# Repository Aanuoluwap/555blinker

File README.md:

# 555 Blinker & ESP32 Projects

This repository contains electronics design projects created using KiCad.

## Projects

### 1. 555 Blinker (Root)

A classic Astable Multivibrator circuit using the NE555 timer IC.

**Components:**
- **U1**: NE555D (SOIC-8)
- **R1**: 1kΩ Resistor (1206)
- **R2**: 68kΩ Resistor (1206)
- **R3**: 8.2kΩ Resistor (1206)
- **C2**: 10µF Tantalum Capacitor (EIA-3216-18)
- **D1**: LED (1206)
- **J1**: 1x02 Pin Header (2.54mm)

**Function:**
The circuit is configured as an astable multivibrator, flashing the LED (D1). The frequency is determined by R2, R3, and C2.

### 2. Project 2: ESP32 Build

Located in `Priject_2__ESP32_build/`.

This project involves an ESP32 microcontroller.
*(Further details to be added)*

## Directory Structure

```
.
├── 555 blinker.kicad_pro    # 555 Blinker Project File
├── 555 blinker.kicad_sch    # Schematic
├── 555 blinker.kicad_pcb    # PCB Layout
└── Priject_2__ESP32_build/  # ESP32 Project Folder
```

## Tools Used

- **KiCad EDA**: [https://www.kicad.org/](https://www.kicad.org/) (Version 8.0 or later recommended)

## License

This project is licensed under the MIT License - see the [LICENSE](LICENSE) file for details.

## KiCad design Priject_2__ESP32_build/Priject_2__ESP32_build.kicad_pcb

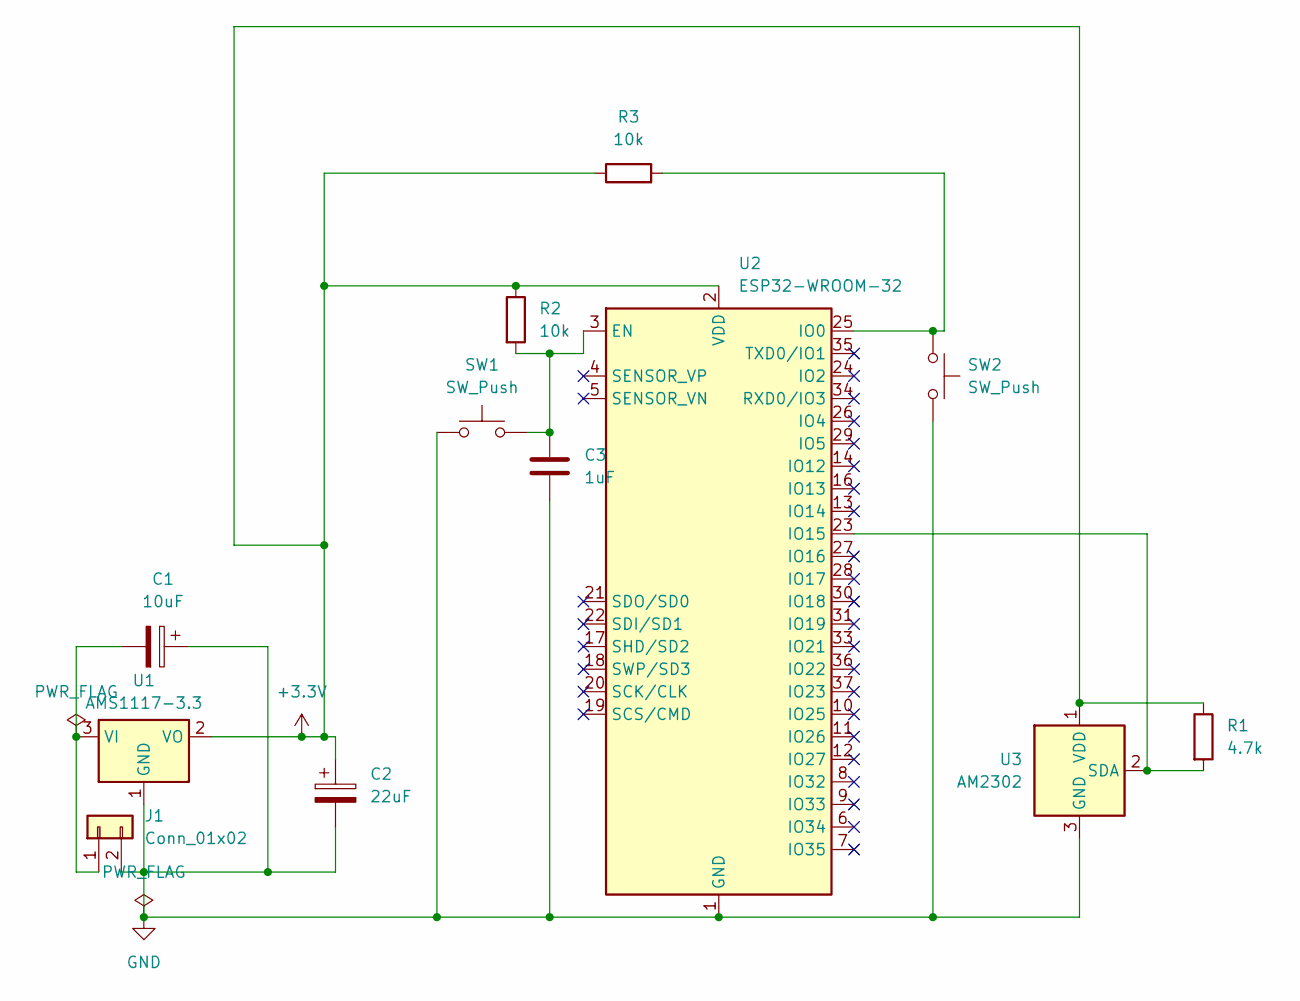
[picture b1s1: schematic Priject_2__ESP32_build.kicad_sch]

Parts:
C1: 10uF; CP_EIA-3216-18_Kemet-A
C2: 22uF; CP_EIA-3216-18_Kemet-A
C3: 1uF; CP_EIA-3216-18_Kemet-A
J1: Conn_01x02; PinHeader_1x02_P2.54mm_Vertical_SMD_Pin1Right
R1: 4.7k; R_1206_3216Metric
R2, R3: 10k; R_1206_3216Metric
SW1, SW2: SW_Push; SW_DIP_SPSTx02_Slide_9.78x7.26mm_W8.61mm_P2.54mm
U1: AMS1117-3.3; SOT-223-3_TabPin2
U2: ESP32-WROOM-32
U3: AM2302; ASAIR_AM2302_P2.54mm_Vertical

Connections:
+3.3V: C2.1, R1.1, R2.1, R3.1, U1.2 (VO), U2.2 (VDD), U3.1 (VDD)
GND: C1.1, C2.2, C3.2, J1.2, SW1.1, SW2.2, U1.1 (GND), U2.1 (GND), U2.15 (GND), U2.38 (GND), U2.39 (GND), U3.3 (GND), U3.4 (GND)
unnamed: C1.2, J1.1, U1.3 (VI)
unnamed: C3.1, R2.2, SW1.2, U2.3 (EN)
unnamed: R3.2, SW2.1, U2.25 (IO0)
unnamed: R1.2, U2.23 (IO15), U3.2 (SDA)

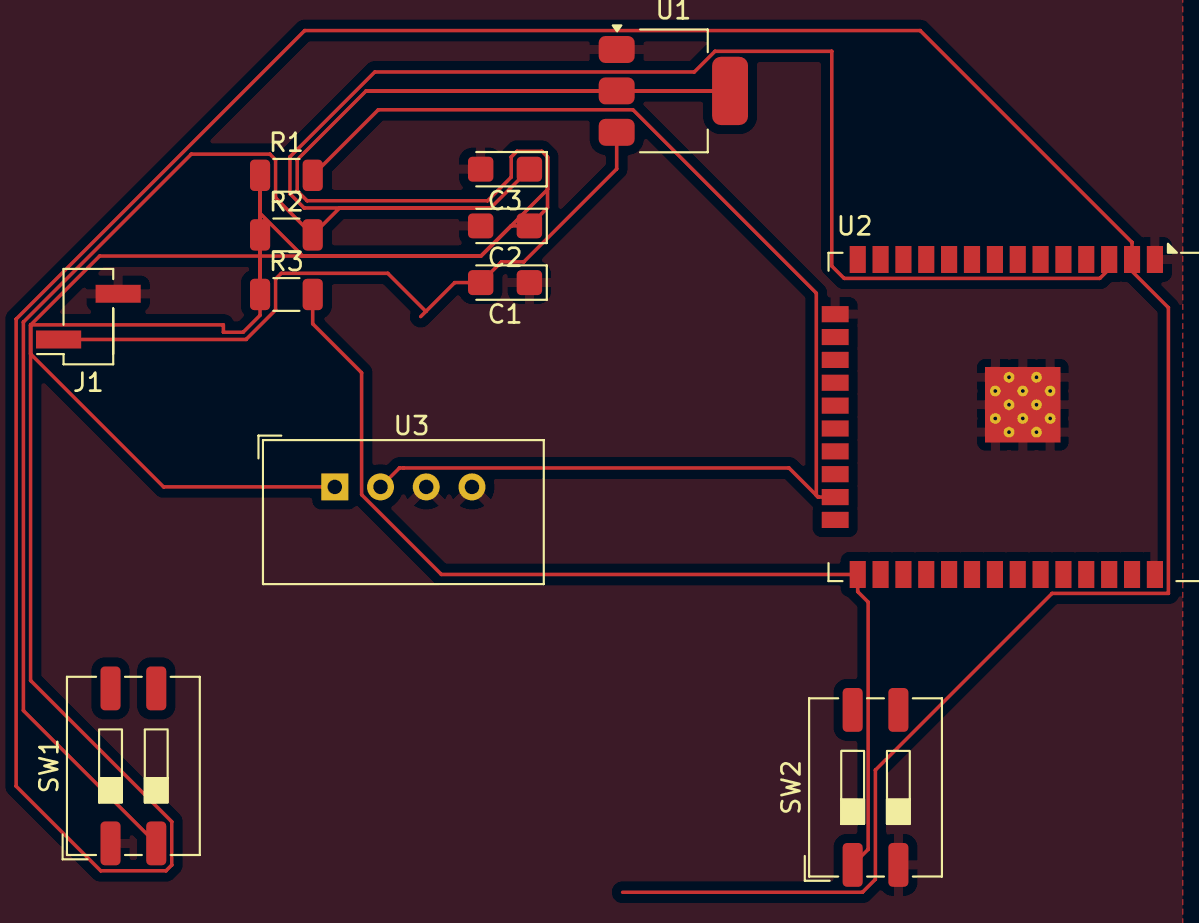
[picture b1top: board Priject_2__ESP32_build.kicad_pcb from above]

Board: 2 copper layers, 12 parts (0 on the bottom side), 6 nets.

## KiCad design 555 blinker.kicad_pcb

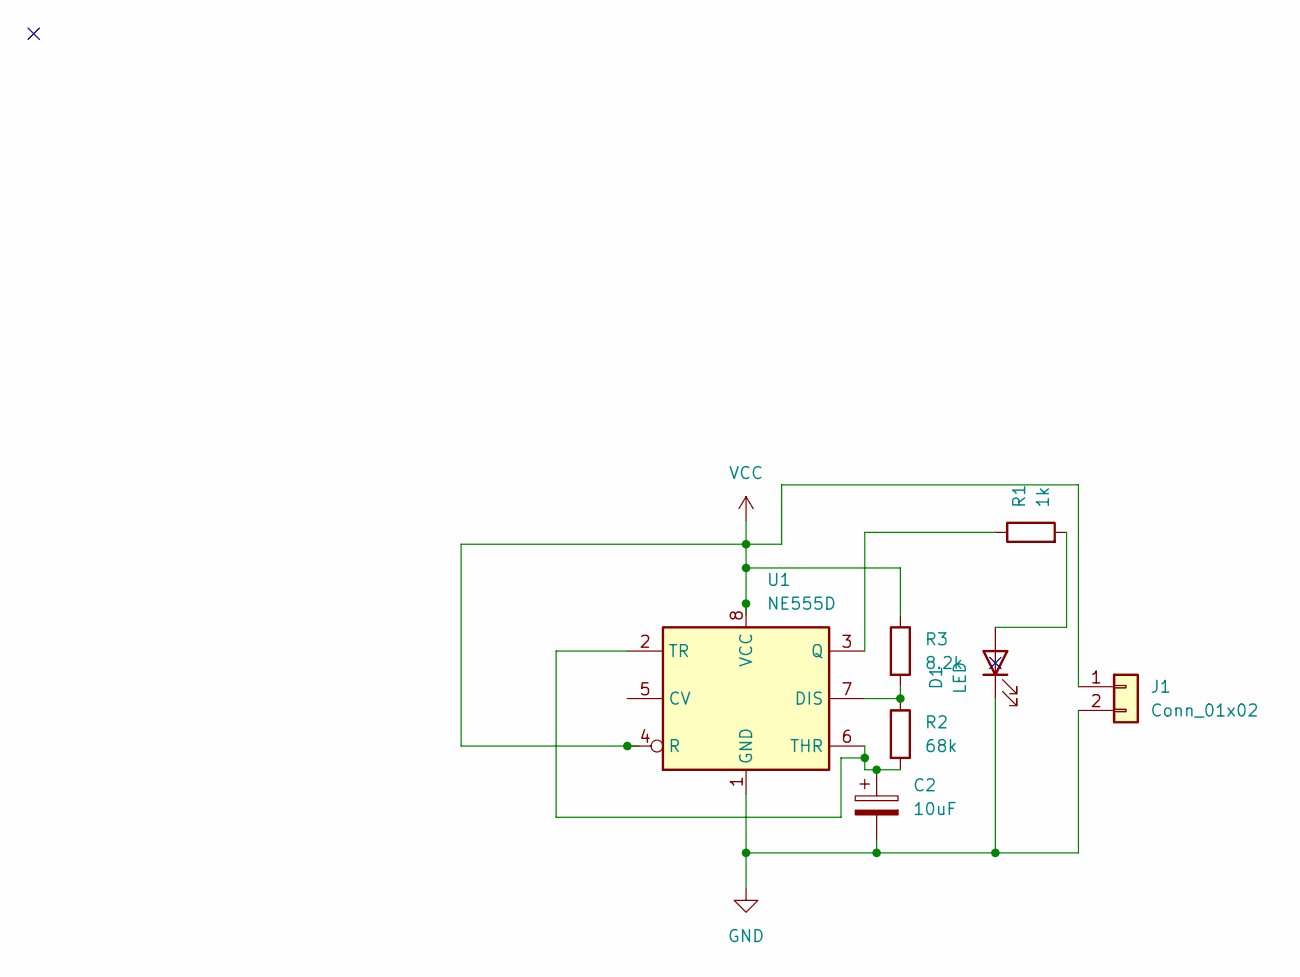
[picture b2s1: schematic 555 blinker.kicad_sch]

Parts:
C2: 10uF; CP_EIA-3216-18_Kemet-A
D1: LED; LED_1206_3216Metric
J1: Conn_01x02; PinHeader_1x02_P2.54mm_Vertical
R1: 1k; R_1206_3216Metric
R2: 68k; R_1206_3216Metric
R3: 8.2k; R_1206_3216Metric
U1: NE555D; SOIC-8_3.9x4.9mm_P1.27mm

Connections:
GND: C2.2, D1.1 (K), J1.2, U1.1 (GND)
unnamed: D1.2 (A), R1.2
unnamed: R2.1, R3.2, U1.7 (DIS)
unnamed: R1.1, U1.3 (Q)
unnamed: C2.1, R2.2, U1.2 (TR), U1.6 (THR)
VCC: J1.1, R3.1, U1.4 (R), U1.8 (VCC)

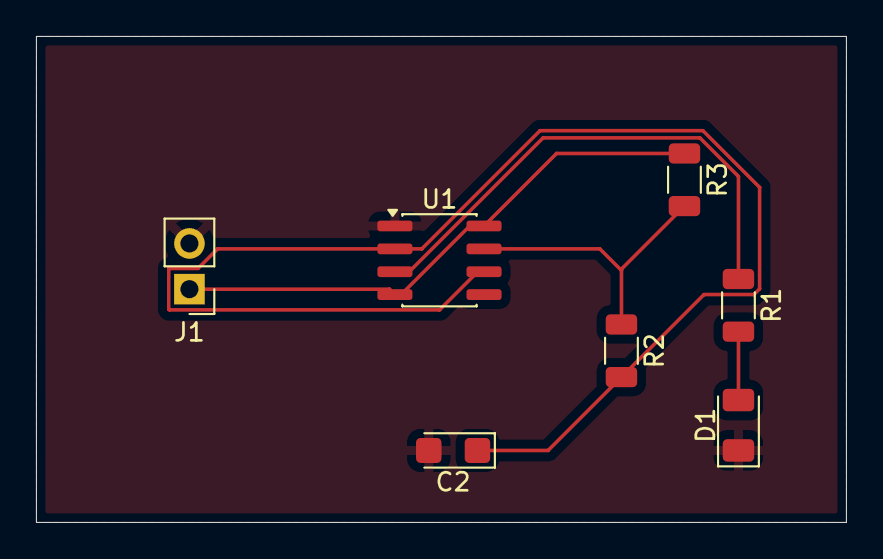
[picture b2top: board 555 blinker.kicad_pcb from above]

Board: 2 copper layers, 45.0 x 27.0 mm, 7 parts (0 on the bottom side), 6 nets.

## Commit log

2025-12-10 Initial committ
2025-12-10 Clean up repository and add README.md
    Ignored and removed KiCad backup directories, report files, and other generated artifacts.
    Added a README.md file describing the 555 Blinker and ESP32 projects.
2025-12-10 Clean up repository, add README and MIT License
    - Removed KiCad backup directories and generated report files.
    - Updated .gitignore to exclude backups and reports.
    - Added README.md describing the projects.
    - Added MIT License with owner Aanuoluwapo Oniyide.
2025-12-10 Add 3D view image of the PCB to README
    - Created 'images' directory.
    - Added '555_blinker_3d_view.png'.
    - Updated README.md to display the image.
